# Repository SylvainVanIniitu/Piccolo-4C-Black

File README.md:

# PiccoloBlack
MIDI Stochastic Sequencer

Project of a stochastic MIDI sequencer developped since a few years (2016) in solo
I decided in 2023 to make its code and the schematics public and open to modifications by others

Piccolo is a polyrythmic errorist and stochastic MIDI sequencer, slightly verging towards a proto-programmable interpreter, very apt to generative and process-based music.the current version is based on the Teensy 4.1 architecture and MIDI protocol.    The previous versions  were relying on Teensy 3.5 and earlier ATmega2560.   The step to Teensy3.5 had provided 10x more precision in time, and 10x more memory.   the best place to see some movies of the action of the current prototypes is on my fb page : https://www.facebook.com/Piccolo-MIDI-sequencer-230847087794581/ 

i also compiled a few videos here : https://www.youtube.com/watch?v=yQdNbUFVs8c

several records have been released as Sylvain van iniitu or 4LLP4 CH1N0, using Piccolo as its main core

the current software version running the sequencer, and fully written in C, features :

MIDI in
MIDI out
OLED screen ( 4 lines of 20 characters ), in place of LCD screen
tap tempo ( different styles )
4 time-independent layers
64 layer memories ( to store layers and load then when necessary )
Unlimited duration loops ( unless you consider a maximum of 4 years as a limitation.. ), that can be independent.   Precision of 1 msec.  full 16 Channel capacity ( 16 channel can be used on each 4 layers )
Unlimited notes by layer ( up till the time the memory is full… we haven’t got there yet when playing )
more than 100 matrix transformations of the sequences ( delay, variable delay, transposition, harmonization, modulation, tonulation, reverse, inverse, simplification, etc... ) - most of it is crazy stuff, you'll just need to dive in the manual to get a clue
modulation of the layers by sequences : useful for (ir)regular transpositions, by note or by layer, modification of velocity, modification of length of note, etc.
possibility to program regular events, launching a transformation, either in absolute time, or after a certain repetition of one (or several) layers
sending CC to any channel, either time-based ( ex. modifying the length of a reverb every 30 sec ), or by note ( modifying it every 5 notes )
possibility to save and load layers as .txt files on SD cards. you can simply edit those .txt files on any text editor on any platform
reading .MIDI files on the SD card ; possibility to glitch those at core level
USB cable alimentation - does not require a computer to work
non-destructive and non-permanent delays, under various forms : regular delay, quad delay ( adapted from Tambour ), fractal delay ( adapted from Dende )
step sequencer : material 4 steps, but virtual from 2 to 127 steps ; you can program it with any note from any channel

Big thanks to : Ikue Mori, Steve Reich, Two Lone Swordsmen, Christian Wolff, Seth Horvitz (Sutekh), Phillus, Burnt Friedman, Cylob and Actress for most inspiration on building this thing.

Please send me the music you make with this sequencer !

If you make a short run of them, please send me one !

If you want to support, please buy my music at bandcamp E42.A8 : https://e42a8.bandcamp.com 

and if you like it : buy some more at https://stilll-off.bandcamp.com/album/sylvain-van-iniitu-plays-django-reinhardt 

or http://tanukirecords.bandcamp.com/album/vulgar-display-of-debug-vol-3-thrift-thrift-horatio

and yes, invite me for a workshop somewhere, and let me play a concert in your city ! 

P x L x U x R

sylvain van iniitu

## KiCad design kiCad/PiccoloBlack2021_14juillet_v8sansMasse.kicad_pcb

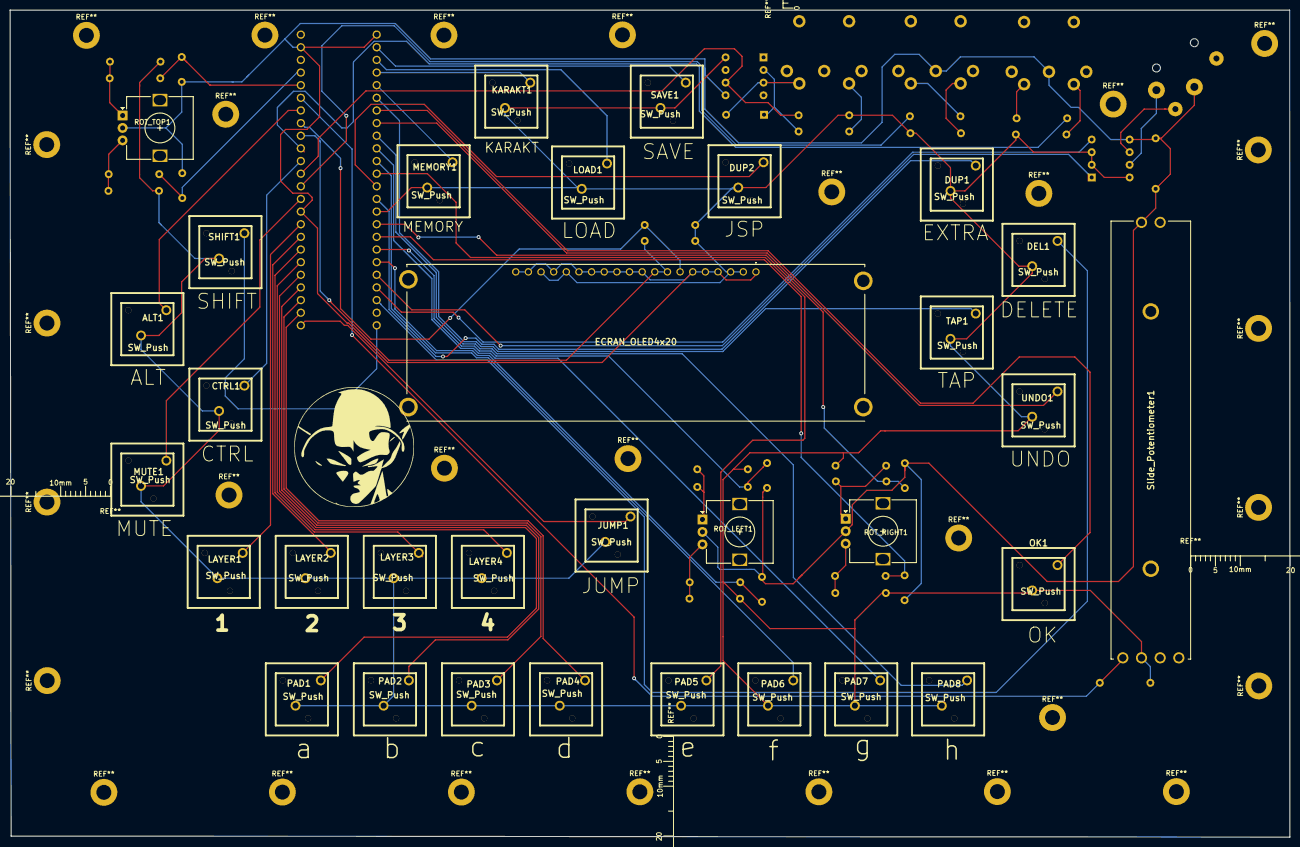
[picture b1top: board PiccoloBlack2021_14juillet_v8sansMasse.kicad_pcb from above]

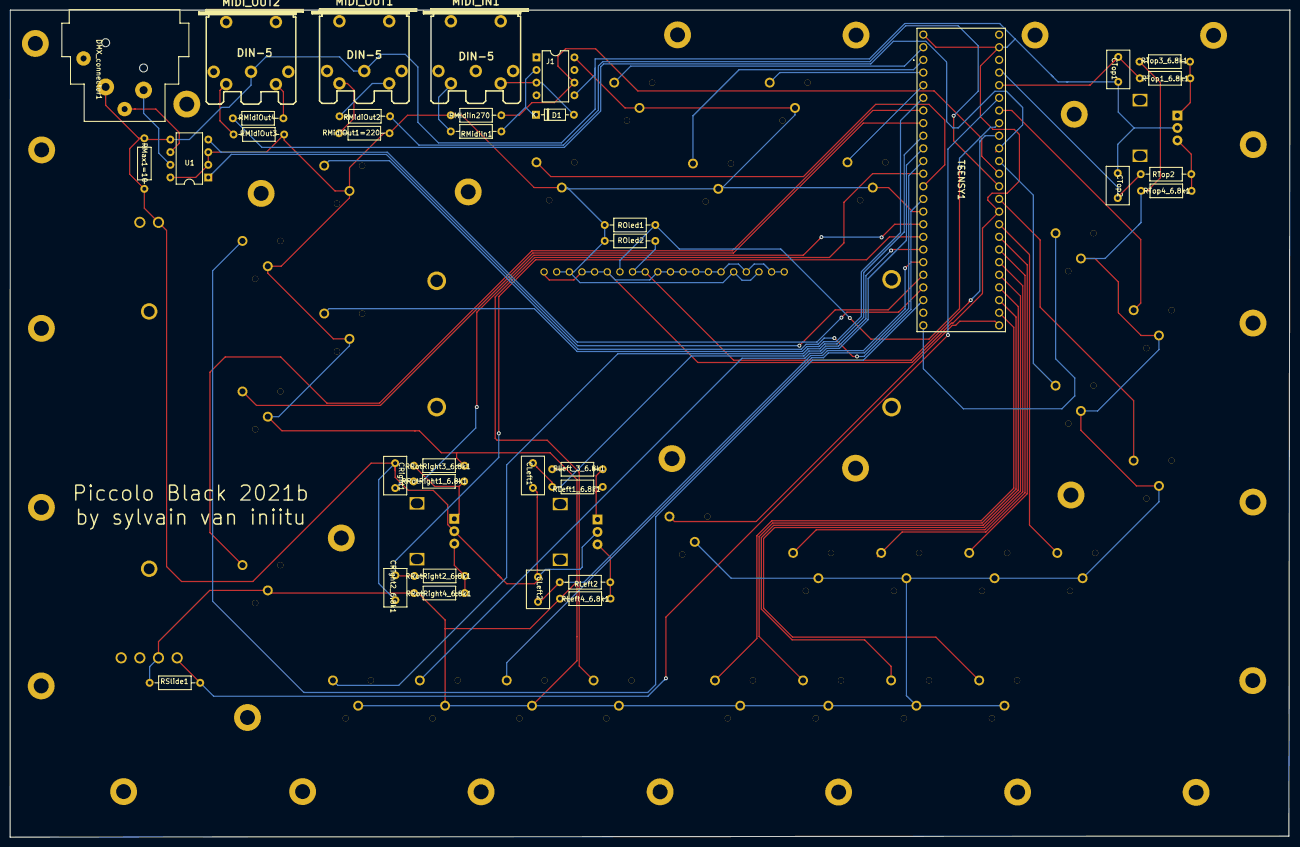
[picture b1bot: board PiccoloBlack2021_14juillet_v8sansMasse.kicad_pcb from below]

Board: 2 copper layers, 257.1 x 166.2 mm, 68 parts (36 on the bottom side), 58 nets.

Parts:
ALT1: SW_Push; PCB_PUSH2
CLeft1, CLeft2: C 0.01u = 103; C_Disc_D7.5mm_W4.4mm_P5.00mm
CRight1, CRight2_6.8k1: C 0.01u = 103; C_Disc_D7.5mm_W4.4mm_P5.00mm
CTRL1: SW_Push; PCB_PUSH2
CTop1, CTop2: C 0.01u = 103; C_Disc_D7.5mm_W4.4mm_P5.00mm
D1: 1N914; D_DO-35_SOD27_P7.62mm_Horizontal
DEL1: SW_Push; PCB_PUSH2
DMX_connector1: NC3FBH2; Jack_XLR_Neutrik_NC3FBH2_Horizontal
DUP1, DUP2: SW_Push; PCB_PUSH2
ECRAN_OLED4x20: NHD-0420CW-AW3; NHD0420CWAW3
J1: Conn_02x04_Counter_Clockwise; DIP-8_W7.62mm
JUMP1: SW_Push; PCB_PUSH2
KARAKT1: SW_Push; PCB_PUSH2
LAYER1, LAYER2, LAYER3, LAYER4: SW_Push; PCB_PUSH2
LOAD1: SW_Push; PCB_PUSH2
MEMORY1: SW_Push; PCB_PUSH2
MIDI_IN1: DIN-5; din-5
MIDI_OUT1, MIDI_OUT2: DIN-5; din-5
MUTE1: SW_Push; PCB_PUSH2
OK1: SW_Push; PCB_PUSH2
PAD1, PAD2, PAD3, PAD4, PAD5, PAD6, PAD7, PAD8: SW_Push; PCB_PUSH2
RLeft1_6.8k1, RLeft2, RLeft4_6.8k1: _6.8k; R_Axial_DIN0207_L6.3mm_D2.5mm_P10.16mm_Horizontal
RLeft_3_6.8k1: _6.8k; R_Axial_DIN0207_L6.3mm_D2.5mm_P10.16mm_Horizontal
RMIdiIn270: 270; R_Axial_DIN0207_L6.3mm_D2.5mm_P10.16mm_Horizontal
RMax1=10: R 10; R_Axial_DIN0207_L6.3mm_D2.5mm_P10.16mm_Horizontal
RMidiIn1: 220; R_Axial_DIN0207_L6.3mm_D2.5mm_P10.16mm_Horizontal
RMidiOut1=220, RMidiOut2, RMidiOut3, RMidiOut4: 220; R_Axial_DIN0207_L6.3mm_D2.5mm_P10.16mm_Horizontal
ROT_LEFT1: Rotary_Encoder; RotaryEncoder_Alps_EC12E_Vertical_H20mm
ROT_RIGHT1: Rotary_Encoder; RotaryEncoder_Alps_EC12E_Vertical_H20mm
ROT_TOP1: Rotary_Encoder; RotaryEncoder_Alps_EC12E_Vertical_H20mm
ROled1, ROled2: 6,8k; R_Axial_DIN0207_L6.3mm_D2.5mm_P10.16mm_Horizontal
RRotRight1_6.8k1: 6.8k; R_Axial_DIN0207_L6.3mm_D2.5mm_P10.16mm_Horizontal
RRotRight2_6.8k1, RRotRight3_6.8k1, RRotRight4_6.8k1: _6.8k; R_Axial_DIN0207_L6.3mm_D2.5mm_P10.16mm_Horizontal
RSlide1: 3,3k; R_Axial_DIN0207_L6.3mm_D2.5mm_P10.16mm_Horizontal
RTop1_6.8k1, RTop2, RTop3_6.8k1, RTop4_6.8k1: _6.8k; R_Axial_DIN0207_L6.3mm_D2.5mm_P10.16mm_Horizontal
SAVE1: SW_Push; PCB_PUSH2
SHIFT1: SW_Push; PCB_PUSH2
Slide_Potentiometer1: RS60N1219A04
TAP1: SW_Push; PCB_PUSH2
TEENSY1: TEENSY_4.1; TEENSY41sans_trous_du_milieux
U1: MAX485E; DIP-8_W7.62mm
UNDO1: SW_Push; PCB_PUSH2

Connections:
GND: CLeft1.1, CLeft2.1, CRight1.1, CRight2_6.8k1.1, CTop1.1, CTop2.1, DMX_connector1.1, ECRAN_OLED4x20.1, ECRAN_OLED4x20.4, ECRAN_OLED4x20.5, ECRAN_OLED4x20.6, ECRAN_OLED4x20.10, ECRAN_OLED4x20.11, ECRAN_OLED4x20.12, ECRAN_OLED4x20.13, ECRAN_OLED4x20.14, ECRAN_OLED4x20.15, ECRAN_OLED4x20.17, ECRAN_OLED4x20.19, ECRAN_OLED4x20.20, J1.5, MIDI_OUT1.2, MIDI_OUT2.2, RMax1=10.1, RMax1=10.2, ROT_LEFT1.C, ROT_RIGHT1.C, ROT_TOP1.C, Slide_Potentiometer1.5, TEENSY1.G1, TEENSY1.G2, TEENSY1.G3, U1.5
unnamed: ALT1.1, TEENSY1.20
unnamed: ALT1.2, CTRL1.2, DEL1.2, DUP1.2, DUP2.2, ECRAN_OLED4x20.2, ECRAN_OLED4x20.3, ECRAN_OLED4x20.16, ECRAN_OLED4x20.18, J1.8, JUMP1.2, KARAKT1.2, LAYER1.2, LAYER2.2, LAYER3.2, LAYER4.2, LOAD1.2, MEMORY1.2, MUTE1.2, OK1.2, PAD1.2, PAD2.2, PAD3.2, PAD4.2, PAD5.2, PAD6.2, PAD7.2, PAD8.2, RLeft4_6.8k1.2, RLeft_3_6.8k1.1, RMIdiIn270.2, RMidiOut1=220.1, RMidiOut3.1, ROled1.1, ROled2.2, RRotRight3_6.8k1.1, RRotRight4_6.8k1.2, RSlide1.1, RTop3_6.8k1.1, RTop4_6.8k1.2, SAVE1.2, SHIFT1.2, Slide_Potentiometer1.1, TAP1.2, TEENSY1.42, U1.2, U1.3, U1.8, UNDO1.2
unnamed: CLeft1.2, RLeft1_6.8k1.2, TEENSY1.26
unnamed: CLeft2.2, RLeft2.2, TEENSY1.27
unnamed: CRight1.2, RRotRight1_6.8k1.2, TEENSY1.24
unnamed: CRight2_6.8k1.2, RRotRight2_6.8k1.2, TEENSY1.25
unnamed: CTRL1.1, TEENSY1.16
unnamed: CTop1.2, RTop1_6.8k1.2, TEENSY1.22
unnamed: CTop2.2, RTop2.2, TEENSY1.23
unnamed: D1.1, J1.2, RMidiIn1.1
unnamed: D1.2, J1.3, MIDI_IN1.5
unnamed: DEL1.1, TEENSY1.30
unnamed: DMX_connector1.2, U1.7
unnamed: DMX_connector1.3, U1.6
unnamed: DUP1.1, TEENSY1.12
unnamed: DUP2.1, TEENSY1.11
unnamed: ECRAN_OLED4x20.7, ROled1.2, TEENSY1.19
unnamed: ECRAN_OLED4x20.8, ECRAN_OLED4x20.9, ROled2.1, TEENSY1.18
unnamed: J1.6, RMIdiIn270.1, TEENSY1.15
unnamed: JUMP1.1, TEENSY1.33
unnamed: KARAKT1.1, TEENSY1.2
unnamed: LAYER1.1, TEENSY1.41
unnamed: LAYER2.1, TEENSY1.40
unnamed: LAYER3.1, TEENSY1.39
unnamed: LAYER4.1, TEENSY1.38
unnamed: LOAD1.1, TEENSY1.1
unnamed: MEMORY1.1, TEENSY1.3
unnamed: MIDI_IN1.4, RMidiIn1.2
unnamed: MIDI_OUT1.4, RMidiOut1=220.2
unnamed: MIDI_OUT1.5, RMidiOut2.2
unnamed: MIDI_OUT2.4, RMidiOut3.2
unnamed: MIDI_OUT2.5, RMidiOut4.2
unnamed: MUTE1.1, TEENSY1.13
unnamed: OK1.1, TEENSY1.5
unnamed: PAD1.1, TEENSY1.37
unnamed: PAD2.1, TEENSY1.36
unnamed: PAD3.1, TEENSY1.35
unnamed: PAD4.1, TEENSY1.34
unnamed: PAD5.1, TEENSY1.10
unnamed: PAD6.1, TEENSY1.9
unnamed: PAD7.1, TEENSY1.8
unnamed: PAD8.1, TEENSY1.7
unnamed: RLeft1_6.8k1.1, RLeft_3_6.8k1.2, ROT_LEFT1.A
unnamed: RLeft2.1, RLeft4_6.8k1.1, ROT_LEFT1.B
unnamed: RMidiOut2.1, TEENSY1.14
unnamed: RMidiOut4.1, TEENSY1.17
unnamed: ROT_RIGHT1.A, RRotRight1_6.8k1.1, RRotRight3_6.8k1.2
unnamed: ROT_RIGHT1.B, RRotRight2_6.8k1.1, RRotRight4_6.8k1.1
unnamed: ROT_TOP1.A, RTop1_6.8k1.1, RTop3_6.8k1.2
unnamed: ROT_TOP1.B, RTop2.1, RTop4_6.8k1.1
unnamed: RSlide1.2, Slide_Potentiometer1.3, TEENSY1.21
unnamed: SAVE1.1, TEENSY1.57
unnamed: SHIFT1.1, TEENSY1.32
unnamed: TAP1.1, TEENSY1.4
unnamed: TEENSY1.6, UNDO1.1
unnamed: TEENSY1.28, U1.1
unnamed: TEENSY1.29, U1.4

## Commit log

2023-03-25 new gitignore
2023-03-25 first modifications
2023-03-25 small changes
2023-03-25 changement de nom
2023-03-25 here
2023-03-25 minor
2023-04-02 minor fixes
2023-04-02 updating schematics kiCad gerber
2023-04-02 changing folder place for Gerber and kiCad
2023-04-02 Create FUNDING.yml
    funding option
2023-04-02 cleaning up code
2023-04-02 updating support
2023-04-02 renaming files
2023-04-02 taking out vscode folder
2023-04-03 Create README.md
    warning about gerber files
2023-04-03 Add files via upload
    build from 3 april 2023, "Piccolo visiting"
2023-04-16 adding CC list
2023-04-16 Rename List of CC by gear to List of CC by gear.md
2023-04-16 working on kiCad update
2025-01-13 new work in Gaurain
    a few updates, notably the ability to play to Serial ( with uQitll ) from a midi keyboard.
2025-09-17 correction CH set SEQ
2025-09-17 fix set CH SEQ
2025-09-17 FunkyVel fix
2025-09-17 funky fix
2025-09-17 nouvelle PitchForNote
2025-09-17 Update subParts.h
    piccolo Thou25
